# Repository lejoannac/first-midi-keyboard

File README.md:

# first-midi-keyboard
My first time creating a midi keyboard pcb in KICAD

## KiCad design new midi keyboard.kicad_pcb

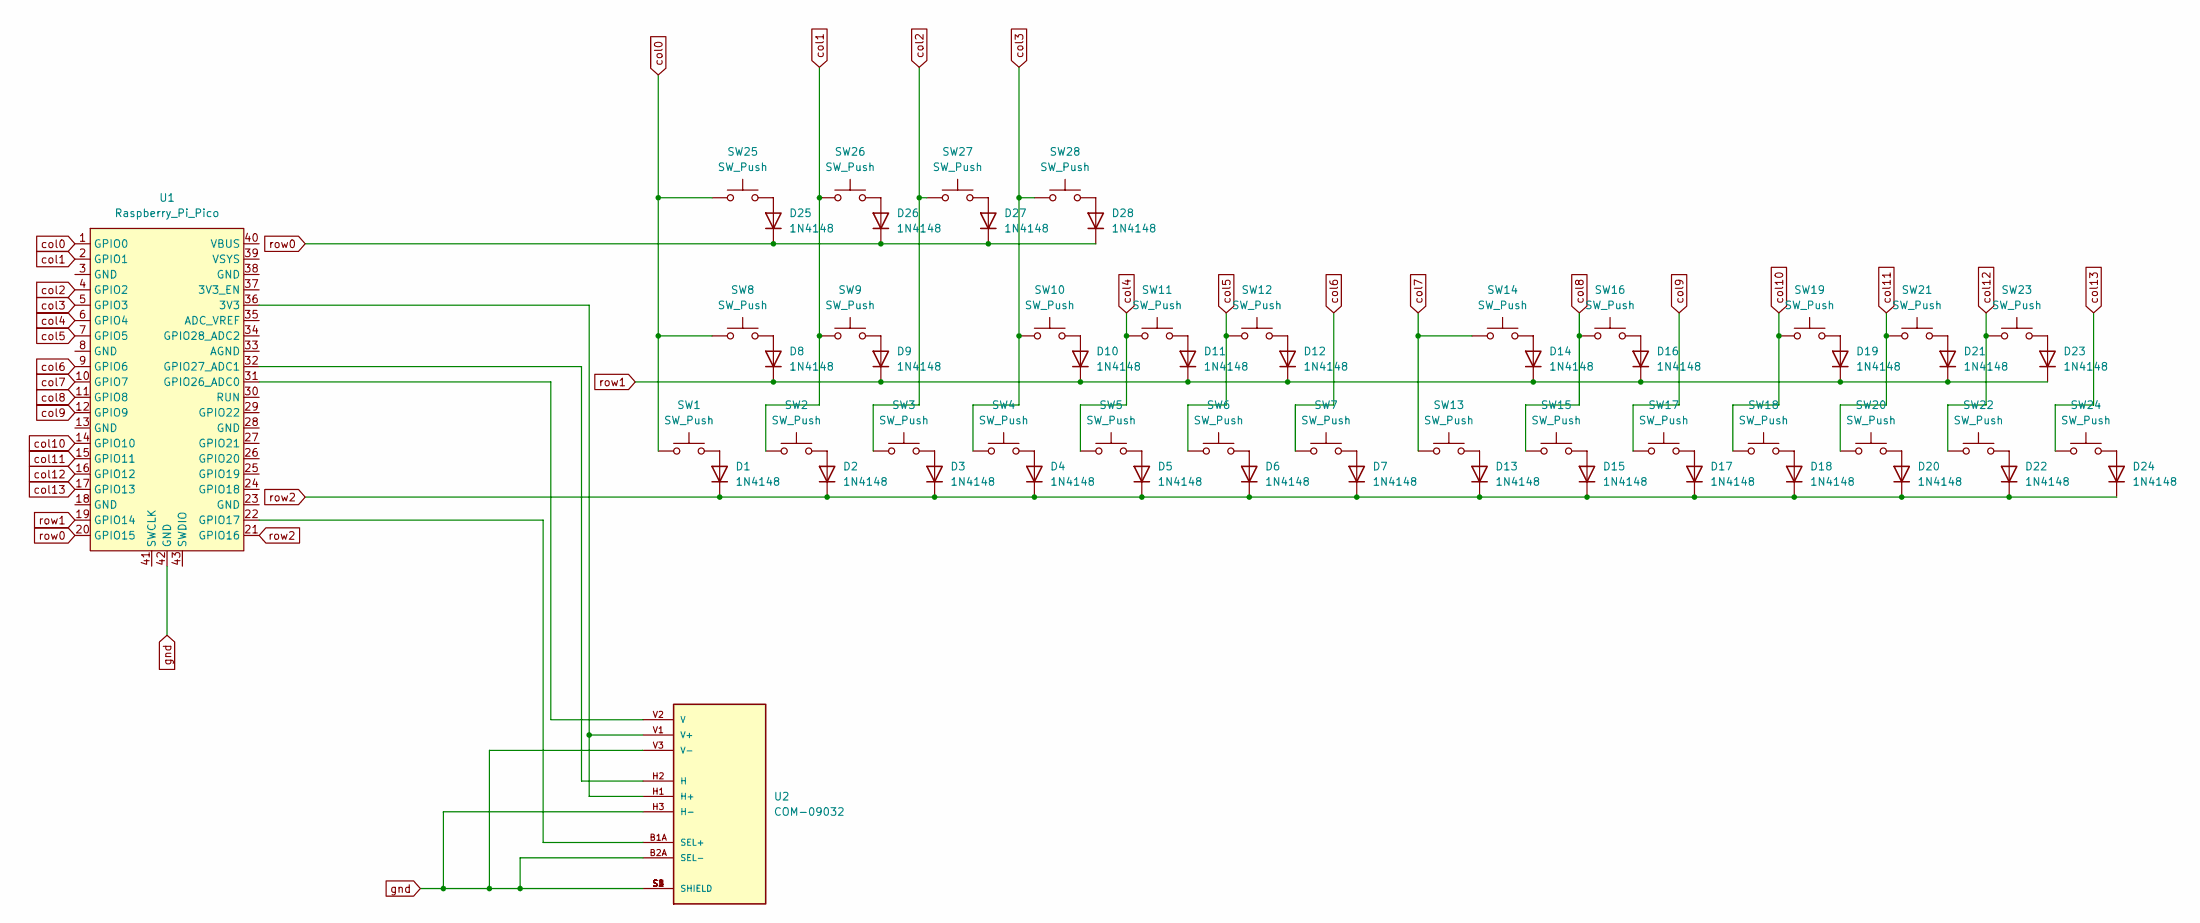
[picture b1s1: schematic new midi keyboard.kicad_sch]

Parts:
D1, D2, D3, D4, D5, D6, D7, D8, D9, D10, D11, D12, D13, D14, D15, D16, D17, D18, D19, D20, D21, D22, D23, D24, D25, D26, D27, D28: 1N4148; D_DO-35_SOD27_P7.62mm_Horizontal
SW1, SW2, SW3, SW4, SW5, SW6, SW7, SW8, SW9, SW10, SW11, SW12, SW13, SW14, SW15, SW16, SW17, SW18, SW19, SW20, SW21, SW22, SW23, SW24, SW25, SW26, SW27, SW28: SW_Push; MX_PCB_1.00unew
U1: Raspberry_Pi_Pico
U2: COM-09032; XDCR_COM-09032; PARTREV N/A

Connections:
unnamed: D1.2 (A), SW1.2
unnamed: D2.2 (A), SW2.2
unnamed: D3.2 (A), SW3.2
unnamed: D4.2 (A), SW4.2
unnamed: D5.2 (A), SW5.2
unnamed: D6.2 (A), SW6.2
unnamed: D7.2 (A), SW7.2
unnamed: D8.2 (A), SW8.2
unnamed: D9.2 (A), SW9.2
unnamed: D10.2 (A), SW10.2
unnamed: D11.2 (A), SW11.2
unnamed: D12.2 (A), SW12.2
unnamed: D13.2 (A), SW13.2
unnamed: D14.2 (A), SW14.2
unnamed: D15.2 (A), SW15.2
unnamed: D16.2 (A), SW16.2
unnamed: D17.2 (A), SW17.2
unnamed: D18.2 (A), SW18.2
unnamed: D19.2 (A), SW19.2
unnamed: D20.2 (A), SW20.2
unnamed: D21.2 (A), SW21.2
unnamed: D22.2 (A), SW22.2
unnamed: D23.2 (A), SW23.2
unnamed: D24.2 (A), SW24.2
unnamed: D25.2 (A), SW25.2
unnamed: D26.2 (A), SW26.2
unnamed: D27.2 (A), SW27.2
unnamed: D28.2 (A), SW28.2
unnamed: U1.36 (3V3), U2.H1 (H+), U2.V1 (V+)
unnamed: U1.22 (GPIO17), U2.B1A (SEL+)
unnamed: U1.31 (GPIO26_ADC0), U2.V2 (V)
unnamed: U1.32 (GPIO27_ADC1), U2.H2 (H)
col0: SW1.1, SW8.1, SW25.1, U1.1 (GPIO0)
col1: SW2.1, SW9.1, SW26.1, U1.2 (GPIO1)
col2: SW3.1, SW27.1, U1.4 (GPIO2)
col3: SW4.1, SW10.1, SW28.1, U1.5 (GPIO3)
col4: SW5.1, SW11.1, U1.6 (GPIO4)
col5: SW6.1, SW12.1, U1.7 (GPIO5)
col6: SW7.1, U1.9 (GPIO6)
col7: SW13.1, SW14.1, U1.10 (GPIO7)
col8: SW15.1, SW16.1, U1.11 (GPIO8)
col9: SW17.1, U1.12 (GPIO9)
col10: SW18.1, SW19.1, U1.14 (GPIO10)
col11: SW20.1, SW21.1, U1.15 (GPIO11)
col12: SW22.1, SW23.1, U1.16 (GPIO12)
col13: SW24.1, U1.17 (GPIO13)
gnd: U1.42 (GND), U2.B2A (SEL-), U2.H3 (H-), U2.S1 (SHIELD), U2.S2 (SHIELD), U2.S3 (SHIELD), U2.S4 (SHIELD), U2.V3 (V-)
row0: D25.1 (K), D26.1 (K), D27.1 (K), D28.1 (K), U1.20 (GPIO15)
row1: D8.1 (K), D9.1 (K), D10.1 (K), D11.1 (K), D12.1 (K), D14.1 (K), D16.1 (K), D19.1 (K), D21.1 (K), D23.1 (K), U1.19 (GPIO14)
row2: D1.1 (K), D2.1 (K), D3.1 (K), D4.1 (K), D5.1 (K), D6.1 (K), D7.1 (K), D13.1 (K), D15.1 (K), D17.1 (K), D18.1 (K), D20.1 (K), D22.1 (K), D24.1 (K), U1.21 (GPIO16)

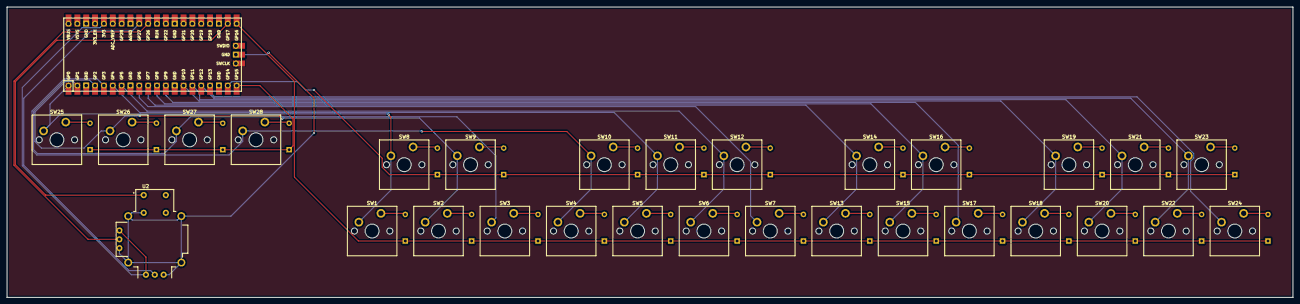
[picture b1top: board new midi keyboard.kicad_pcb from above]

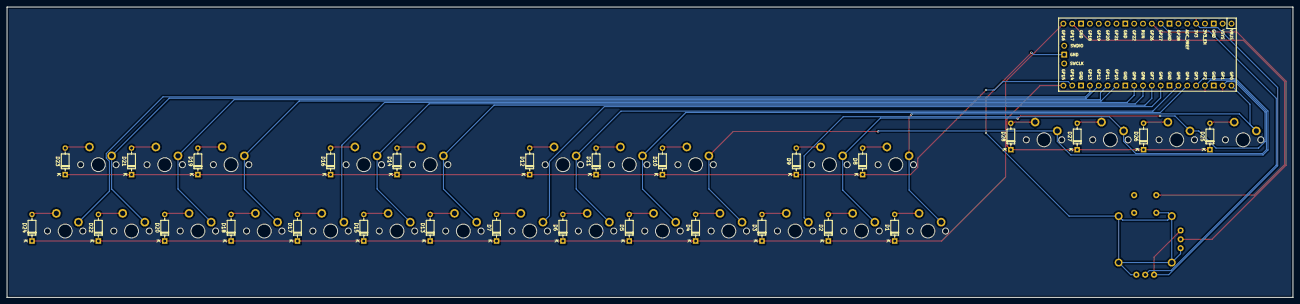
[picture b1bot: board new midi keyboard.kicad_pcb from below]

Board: 2 copper layers, 369.1 x 83.4 mm, 58 parts (28 on the bottom side), 50 nets.

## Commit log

2024-06-27 All gerber files
2024-06-27 Kicad files
